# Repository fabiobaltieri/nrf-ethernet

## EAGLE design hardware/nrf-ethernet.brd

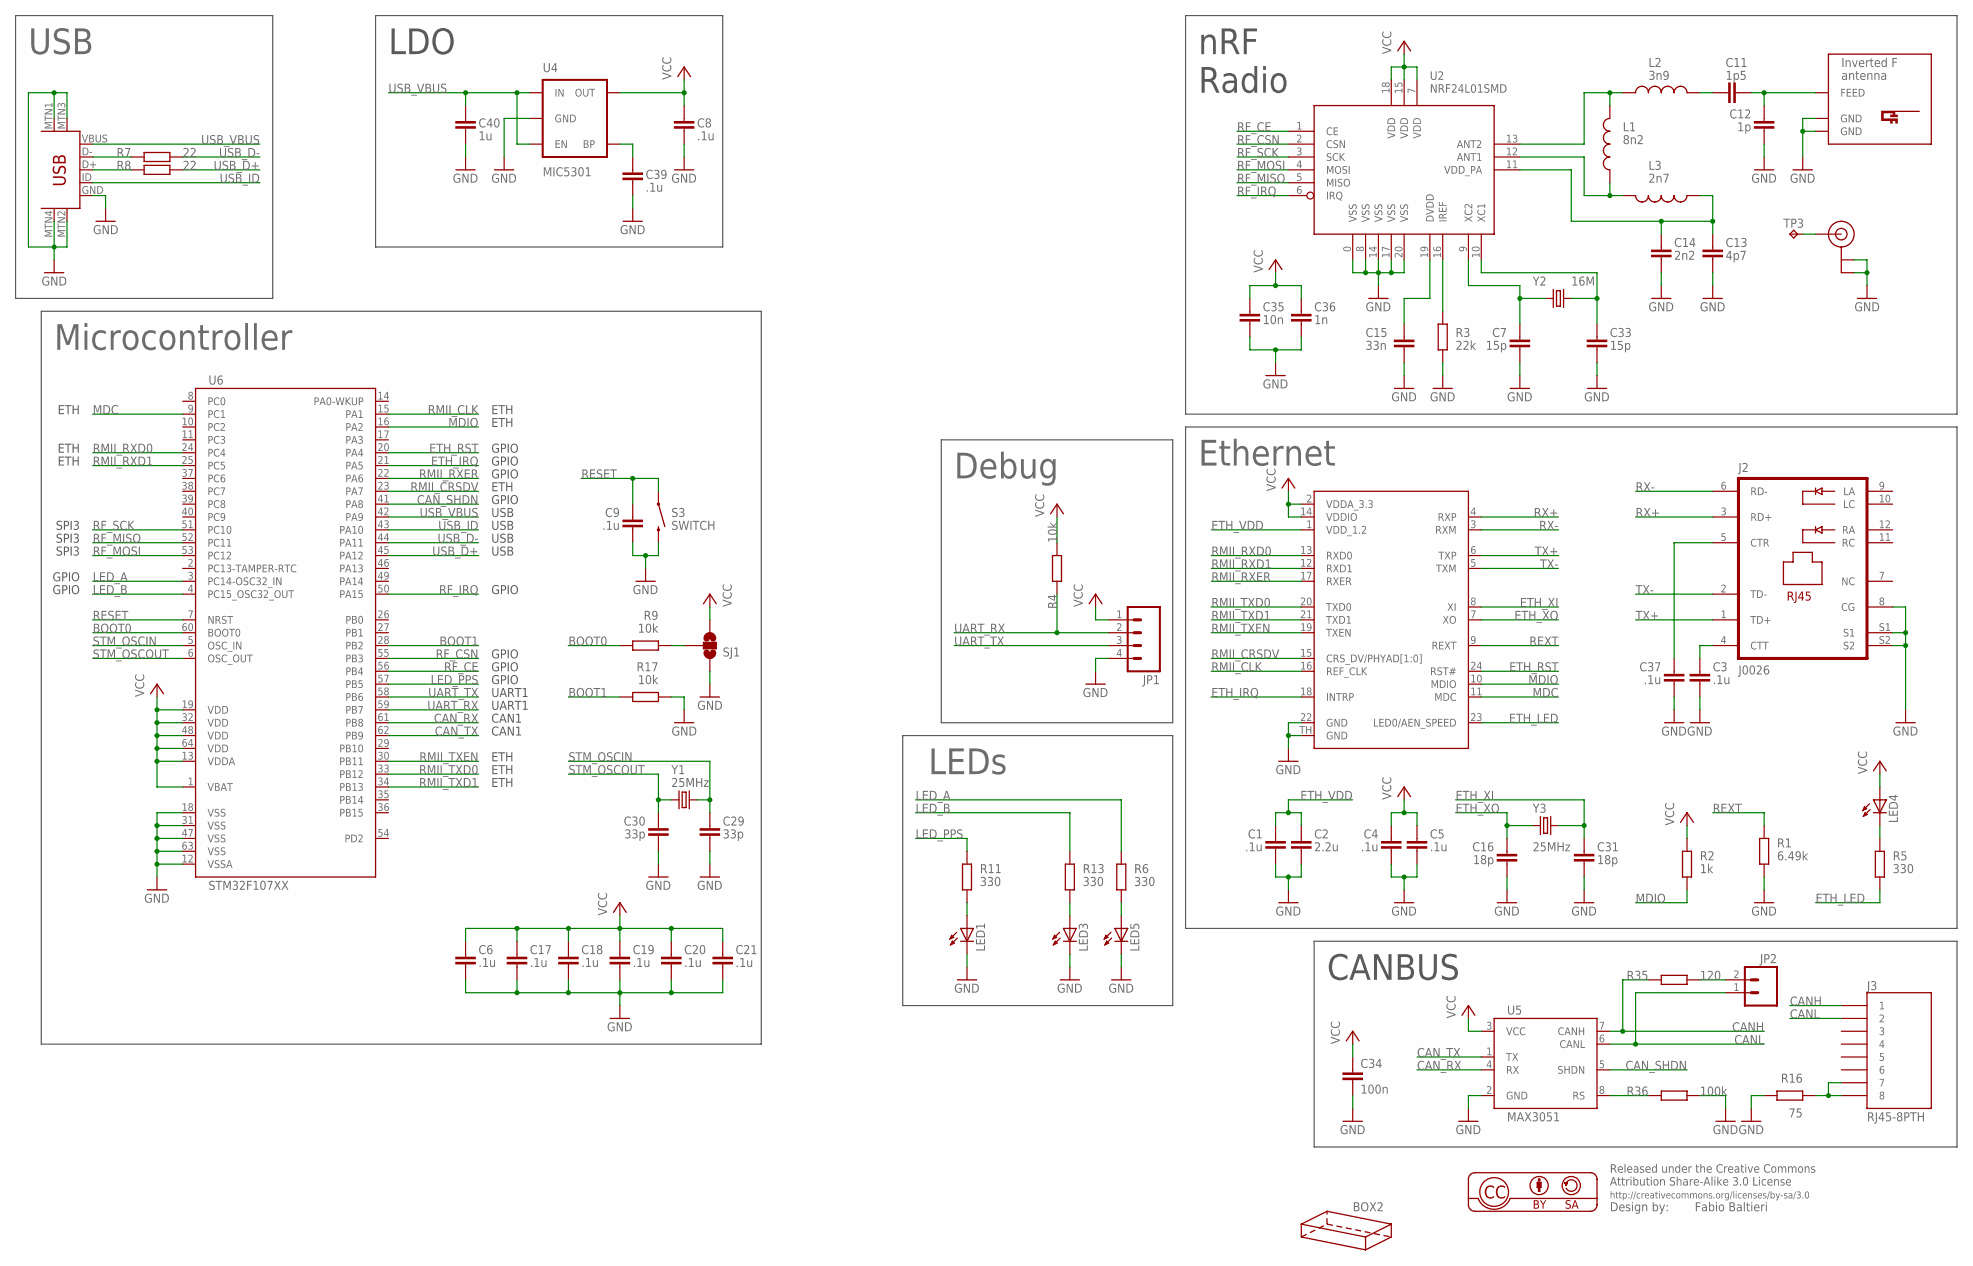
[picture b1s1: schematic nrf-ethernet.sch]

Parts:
BOX2: HAMMOND-BOX-K; 1551K
C1, C3, C4, C5, C6, C8, C9, C17, C18, C19, C20, C21, C37, C39: .1u; C0603
C2: 2.2u; C0603
C7, C33: 15p; C0603
C11: 1p5; C0603
C12: 1p; C0603
C13: 4p7; C0603
C14: 2n2; C0603
C15: 33n; C0603
C16, C31: 18p; C0603
C29, C30: 33p; C0603
C34: 100n; C0603
C35: 10n; C0603
C36: 1n; C0603
C40: 1u; C0603
J2: J0026; PJ-J0
J3: RJ45-8PTH; RJ45-8
JP1: M04PTH; 1X04
JP2: M02PTH; 1X02
L1: 8n2; 0603
L2: 3n9; 0603
L3: 2n7; 0603
LED1, LED3, LED4, LED5: LEDCHIPLED_0805; CHIPLED_0805
R1: 6.49k; R0603
R2: 1k; R0603
R3: 22k; R0603
R4, R9, R17: 10k; R0603
R5, R6, R11, R13: 330; R0603
R7, R8: 22; R0603
R16: 75; R0805
R35: 120; R0805
R36: 100k; R0603
S3: SWITCH; TACTILE_SWITCH_SMD
SJ1: SOLDERJUMPER_2WAYS; SJ_3
TP3: TPTP08SQ; TP08SQ
U1: KSZ8081RNA; QFN24
U2: NRF24L01SMD; QFN20
U4: MIC5301; SOT23-5
U5: MAX3051; SO08
U6: STM32F107XX; LQFP64
U$4: USB-MINIB-5PIN; USB-MINIB
U$5: INVERTED_F_ANTENNA-2; DN007-2
U$6: U.FL
Y1, Y3: 25MHz; CRYSTAL-SMD-5X3
Y2: 16M; CRYSTAL-SMD-5X3

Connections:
BOOT0: R9.2, U6.60 (BOOT0)
BOOT1: R17.2, U6.28 (PB2)
CANH: J3.1, R35.1, U5.7 (CANH)
CANL: J3.2, JP2.1, U5.6 (CANL)
CAN_RX: U5.4 (RX), U6.61 (PB8)
CAN_SHDN: U5.5 (SHDN), U6.41 (PA8)
CAN_TX: U5.1 (TX), U6.62 (PB9)
ETH_IRQ: U1.18 (INTRP), U6.21 (PA5)
ETH_LED: R5.1, U1.23 (LED0/AEN_SPEED)
ETH_RST: U1.24 (RST#), U6.20 (PA4)
ETH_VDD: C1.1, C2.1, U1.1 (VDD_1.2)
ETH_XI: C31.1, U1.8 (XI), Y3.3 (2)
ETH_XO: C16.1, U1.7 (XO), Y3.1
GND: C1.2, C2.2, C3.2, C4.2, C5.2, C6.2, C7.2, C8.2, C9.2, C12.2, C13.2, C14.2, C15.2, C16.2, C17.2, C18.2, C19.2, C20.2, C21.2, C29.2, C30.2, C31.2, C33.2, C34.2, C35.2, C36.2, C37.2, C39.2, C40.2, J2.8 (CG), J2.S1, J2.S2, JP1.4, LED1.C, LED3.C, LED5.C, R1.1, R3.2, R16.1, R17.1, R36.2, S3.3 (2), SJ1.1, U1.22 (GND), U1.TH (GND), U2.0 (VSS), U2.8 (VSS), U2.14 (VSS), U2.17 (VSS), U2.20 (VSS), U4.2 (GND), U5.2 (GND), U6.12 (VSSA), U6.18 (VSS), U6.31 (VSS), U6.47 (VSS), U6.63 (VSS), U$4.GND, U$4.MTN1 (MTN2), U$4.MTN2 (MTN3), U$4.MTN3 (MTN1), U$4.MTN4, U$5.GND, U$5.GND@1 (GND), U$6.P$1 (GND), U$6.P$2 (GND)
LED_A: R6.2, U6.3 (PC14-OSC32_IN)
LED_B: R13.2, U6.4 (PC15_OSC32_OUT)
LED_PPS: R11.2, U6.57 (PB5)
MDC: U1.11 (MDC), U6.9 (PC1)
MDIO: R2.1, U1.10 (MDIO), U6.16 (PA2)
unnamed: LED4.C, R5.2
unnamed: LED1.A, R11.1
unnamed: L1.2, L3.2, U2.12 (ANT1)
unnamed: L1.1, L2.1, U2.13 (ANT2)
unnamed: LED3.A, R13.1
unnamed: C11.1, L2.2
unnamed: C33.1, U2.10 (XC1), Y2.3 (2)
unnamed: C7.1, U2.9 (XC2), Y2.1
unnamed: C3.1, J2.4 (CTT)
unnamed: C37.1, J2.5 (CTR)
unnamed: LED5.A, R6.1
unnamed: C11.2, C12.1, U$5.FEED
unnamed: C13.1, C14.1, L3.1, U2.11 (VDD_PA)
unnamed: C15.1, U2.19 (DVDD)
unnamed: R3.1, U2.16 (IREF)
unnamed: R9.1, SJ1.2
unnamed: TP3.TP, U$6.P$3 (SIGNAL)
unnamed: R7.1, U$4.D-
unnamed: R36.1, U5.8 (RS)
unnamed: R8.1, U$4.D+
unnamed: JP2.2, R35.2
unnamed: J3.7, J3.8, R16.2
unnamed: C39.1, U4.4 (BP)
RESET: C9.1, S3.1, U6.7 (NRST)
REXT: R1.2, U1.9 (REXT)
RF_CE: U2.1 (CE), U6.56 (PB4)
RF_CSN: U2.2 (CSN), U6.55 (PB3)
RF_IRQ: U2.6 (IRQ), U6.50 (PA15)
RF_MISO: U2.5 (MISO), U6.52 (PC11)
RF_MOSI: U2.4 (MOSI), U6.53 (PC12)
RF_SCK: U2.3 (SCK), U6.51 (PC10)
RMII_CLK: U1.16 (REF_CLK), U6.15 (PA1)
RMII_CRSDV: U1.15 (CRS_DV/PHYAD[1:0]), U6.23 (PA7)
RMII_RXD0: U1.13 (RXD0), U6.24 (PC4)
RMII_RXD1: U1.12 (RXD1), U6.25 (PC5)
RMII_RXER: U1.17 (RXER), U6.22 (PA6)
RMII_TXD0: U1.20 (TXD0), U6.33 (PB12)
RMII_TXD1: U1.21 (TXD1), U6.34 (PB13)
RMII_TXEN: U1.19 (TXEN), U6.30 (PB11)
RX+: J2.3 (RD+), U1.4 (RXP)
RX-: J2.6 (RD-), U1.3 (RXM)
STM_OSCIN: C29.1, U6.5 (OSC_IN), Y1.3 (2)
STM_OSCOUT: C30.1, U6.6 (OSC_OUT), Y1.1
TX+: J2.1 (TD+), U1.6 (TXP)
TX-: J2.2 (TD-), U1.5 (TXM)
UART_RX: JP1.2, R4.1, U6.59 (PB7)
UART_TX: JP1.3, U6.58 (PB6)
USB_D+: R8.2, U6.45 (PA12)
USB_D-: R7.2, U6.44 (PA11)
USB_ID: U6.43 (PA10), U$4.ID
USB_VBUS: C40.1, U4.1 (IN), U4.3 (EN), U6.42 (PA9), U$4.VBUS
VCC: C4.1, C5.1, C6.1, C8.1, C17.1, C18.1, C19.1, C20.1, C21.1, C34.1, C35.1, C36.1, JP1.1, LED4.A, R2.2, R4.2, SJ1.3, U1.2 (VDDA_3.3), U1.14 (VDDIO), U2.7 (VDD), U2.15 (VDD), U2.18 (VDD), U4.5 (OUT), U5.3 (VCC), U6.1 (VBAT), U6.13 (VDDA), U6.19 (VDD), U6.32 (VDD), U6.48 (VDD), U6.64 (VDD)

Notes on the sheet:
Ethernet
USB
Debug
CANBUS
nRF
Radio
LDO
LEDs
Microcontroller
GPIO
ETH
SPI3
CAN1
UART1

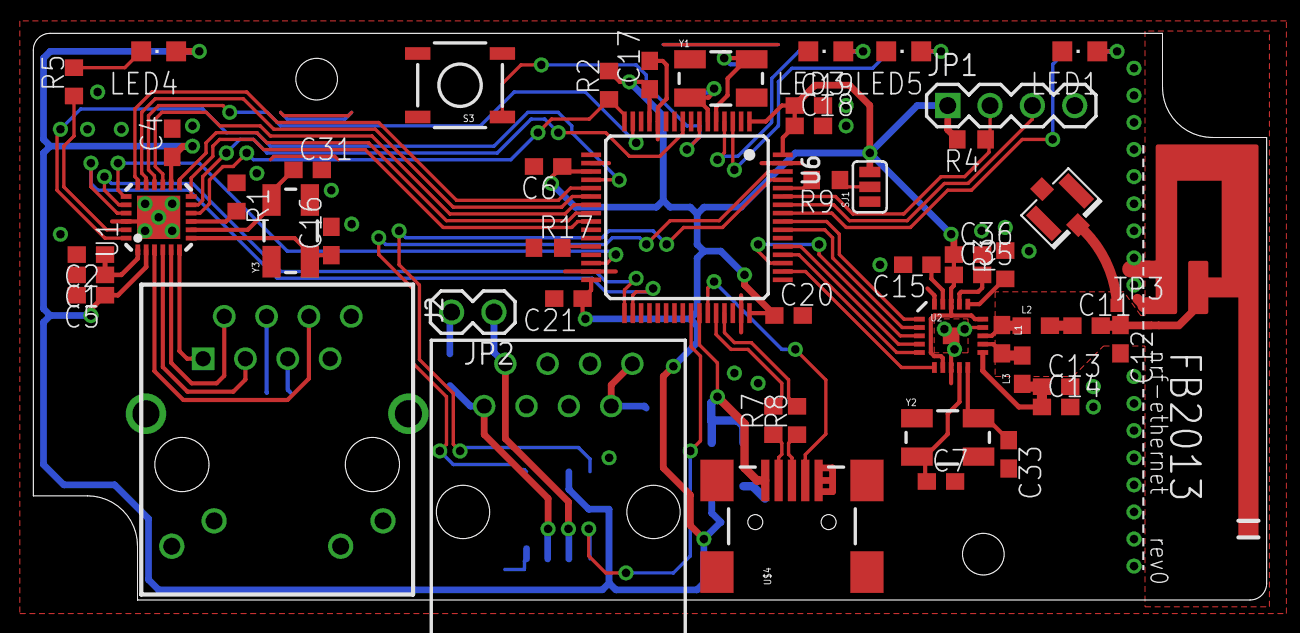
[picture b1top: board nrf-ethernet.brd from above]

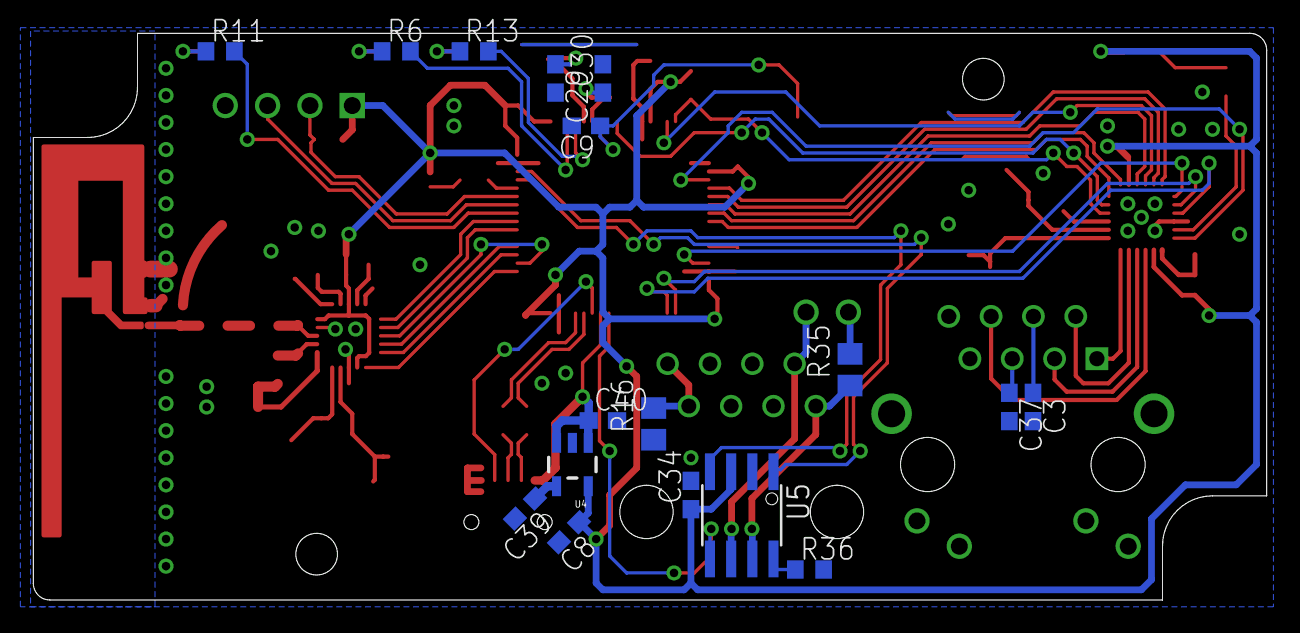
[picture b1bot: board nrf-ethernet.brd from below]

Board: 2 copper layers, 74.0 x 34.0 mm, 71 parts (17 on the bottom side), 71 nets.

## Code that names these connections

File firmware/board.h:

#define BOARD_NAME "nrf-ethernet"

/* MCU configuration */
#define STM32_HSECLK 25000000
#define STM32F10X_CL /* Connectivity Line */

/* Ethernet configuration */
#define BOARD_PHY_RESET()
#define BOARD_PHY_ADDRESS 0
#define BOARD_PHY_ID 0x00221560
#define BOARD_PHY_RMII

/*
 * I/O default setup mappings:
 *   0 - Analog input.
 *   1 - Push Pull output 10MHz.
 *   2 - Push Pull output 2MHz.
 *   3 - Push Pull output 50MHz.
 *   4 - Digital input.
 *   5 - Open Drain output 10MHz.
 *   6 - Open Drain output 2MHz.
 *   7 - Open Drain output 50MHz.
 *   8 - Digital input with PullUp or PullDown resistor depending on ODR.
 *   9 - Alternate Push Pull output 10MHz.
 *   A - Alternate Push Pull output 2MHz.
 *   B - Alternate Push Pull output 50MHz.
 *   C - Reserved.
 *   D - Alternate Open Drain output 10MHz.
 *   E - Alternate Open Drain output 2MHz.
 *   F - Alternate Open Drain output 50MHz.
 */

/*                     Eeee.EE. */
#define VAL_GPIOACRL 0x44828B48
/*                     r..UUUUc */
#define VAL_GPIOACRH 0x84444442
#define VAL_GPIOAODR 0xFFFFFFEF

/*                     UUlrrX.. */
#define VAL_GPIOBCRL 0x4A211488
/*                     ..EEE.CC */
#define VAL_GPIOBCRH 0x88BBB894
#define VAL_GPIOBODR 0xFFFFFFCF

/*                     ..EE..E. */
#define VAL_GPIOCCRL 0x884488B8
/*                     ll.RRR.. */
#define VAL_GPIOCCRH 0x228B8B88
#define VAL_GPIOCODR 0xFFFF3FFF

#define VAL_GPIODCRL 0x88888888
#define VAL_GPIODCRH 0x88888888
#define VAL_GPIODODR 0xFFFFFFFF

#define VAL_GPIOECRL 0x88888888
#define VAL_GPIOECRH 0x88888888
#define VAL_GPIOEODR 0xFFFFFFFF

/* I/O */
#define LED_STATUS_GPIO GPIOC
#define LED_STATUS_RED 15
#define LED_STATUS_GREEN 14

#define led_red_on() palSetPad(LED_STATUS_GPIO, LED_STATUS_RED)
#define led_red_off() palClearPad(LED_STATUS_GPIO, LED_STATUS_RED)
#define led_red_toggle() palTogglePad(LED_STATUS_GPIO, LED_STATUS_RED)
#define led_green_on() palSetPad(LED_STATUS_GPIO, LED_STATUS_GREEN)
#define led_green_off() palClearPad(LED_STATUS_GPIO, LED_STATUS_GREEN)
#define led_green_toggle() palTogglePad(LED_STATUS_GPIO, LED_STATUS_GREEN)

#define LED_RF_GPIO GPIOB
#define LED_RF 5

#define led_rf_on() palSetPad(LED_RF_GPIO, LED_RF)
#define led_rf_off() palClearPad(LED_RF_GPIO, LED_RF)
#define led_rf_toggle() palTogglePad(LED_RF_GPIO, LED_RF)

#define CAN_SHDN_GPIO GPIOA
#define CAN_SHDN 8

#define can_xcvr_enable() palClearPad(CAN_SHDN_GPIO, CAN_SHDN)
#define can_xcvr_disable() palSetPad(CAN_SHDN_GPIO, CAN_SHDN)

#define ETH_RST_GPIO GPIOA
#define ETH_RST 4

#define eth_reset_l() palClearPad(ETH_RST_GPIO, ETH_RST)
#define eth_reset_h() palSetPad(ETH_RST_GPIO, ETH_RST)

#define RF_GPIO GPIOB
#define RF_CSN 3
#define RF_CE 4

#define nrf_cs_l() palClearPad(RF_GPIO, RF_CSN)
#define nrf_cs_h() palSetPad(RF_GPIO, RF_CSN)
#define nrf_ce_l() palClearPad(RF_GPIO, RF_CE)
#define nrf_ce_h() palSetPad(RF_GPIO, RF_CE)

void boardInit(void);

#define pr_info(fmt, args...) chprintf((BaseSequentialStream *)&SDU1, fmt, ## args)
#define pr_debug(fmt, args...) chprintf((BaseSequentialStream *)&SDU1, "%s: " fmt, __func__, ## args)

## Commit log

2013-02-17 rename
2013-02-19 value update
2013-02-24 add silk and gnd vias
2013-02-24 move measurement to meas layer
2013-04-16 hw: fix some part number value
2013-04-19 bootloader: add usbdfu bootloader from generic libopencm3 examples
2013-04-19 bl: increase available SRAM size for the bootloader
2013-04-19 bl: Makefile: add boot target
2013-04-19 bl: new makefile borrowed from power-manager
2013-04-19 bl: increase buffer size to 2k
2013-04-19 bl: update descriptor strings, drop serial
2013-04-19 bl: ensure a disconnect cycle on start
2013-04-19 bl: change i/o and clock for nrf-eth board
2013-04-19 bl: rework bootloader bailout logic to timeout based
2013-04-19 add .gitignore file
2013-04-19 bl: Makefile: add libopencm3 comment
2013-04-19 bl: update license information
2013-04-19 bl: move leave_bootloader code earlier
2013-04-19 bl: leave_bootloader instead of reset
2013-04-19 bl: add variable for CPU = cortex-m3
2013-04-19 firmware: initial import of a blinky ChibiOS project
    We'll see...
2013-04-20 bl: move libopencm3 src path
2013-04-20 fw: set uart rate to 115200 bps
2013-04-20 fw: add serial console
2013-04-20 fw: increase linker ram size to full 64kB
2013-04-20 fw: board: add some pr_ helper function
2013-04-20 fw: blink by toggling
2013-04-21 fw: Makefile: boot target improvements
2013-04-21 fw: wa_blinker -> blinker_wa
2013-04-21 fw: remap canbus pins
2013-04-21 hw: mark led colors in schematic
2013-04-21 fw: clean LEDs defines
2013-04-21 fw: set all GPIO configuration
2013-04-21 fw: add gpio control friendly macros
2013-04-21 fw: compile in lwip and MAC support
2013-04-21 fw: add STM32_MAC settings
2013-04-22 fw: console: rename threads to ps
2013-04-22 console: allow to pass a serial stream on init
2013-04-22 fw: add usb support and soft-reset via usb for comfy reprogramming
2013-04-24 fw: add blink threads and API
2013-04-24 fw: drop extra whitespace in hello.c
2013-04-24 bootloader: leave at step 13
2013-04-29 fw: change blinker to heartbeat
2013-04-29 fw: enable SPI3
2013-04-29 fw: lwipopts: enable DHCP and DNS support
2013-04-29 fw: enable external interrupt stubs
2013-04-29 fw: add nrf24l01p driver
2013-04-29 fw: enable lwip thread
2013-04-29 lwipopts: set hostname
2013-04-30 fw: board: set phy id, through it's not really used
2013-05-01 fw: use struct qualifier for threads
2013-05-01 fw: set heartbeat to lowprio and nrf_radio to normalprio+1
2013-05-04 fw: implement nrf packet send
2013-05-04 fw: move radio blink in irq handler
2013-05-07 fw: add data and data_dump command
2013-05-07 fw: add data locking
2013-05-08 fw: add basic httpd
2013-05-08 fw: add http output buffering
2013-05-08 fw: add path handling
2013-05-08 fw: rename seq reference to net for consistency
2013-05-08 fw: add some path
2013-05-08 fw: trach sequence number
2013-05-08 fw: add json stub
2013-06-22 fw: update usb cdc API
2013-06-22 fw: add json data output implementation
2013-06-22 debug: move print defines to USB device
2013-06-29 fw: fix json print when first entry is clean
2013-06-30 fw: fix stale lock on table full
2013-07-01 fw: rename streams to paths
2013-07-01 fw: add sendraw stubs
2013-07-01 fw: move netbuf_delete after the url callback
2013-07-02 fw: add url and hdr pointers to url callbacks
2013-07-02 fw: accept POST requests
2013-07-02 fw: include terminator in HTTP_VER
2013-07-02 fw: rename GET_ defines to HTTP_
2013-07-02 fw: pass header and data to http handlers
2013-07-03 fw: add sendraw implementation
2013-11-10 fw: lwip: increase stack size to 1536 bytes
2013-12-26 fw: add missing nrf_frames.h
2013-12-26 fw: add net information console command
2013-12-26 fw: increase tcp and netconn allocation
2013-12-26 fw: httpd: include own header
2013-12-26 fw: add rawd code

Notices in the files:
parts and their libraries:
SparkFun-Connectors: Licensing: CC v3.0 Share-Alike You are welcome to use this library for commercial purposes.
balto: Released under the Creative Commons
balto: http://creativecommons.org/licenses/by-sa/3.0
